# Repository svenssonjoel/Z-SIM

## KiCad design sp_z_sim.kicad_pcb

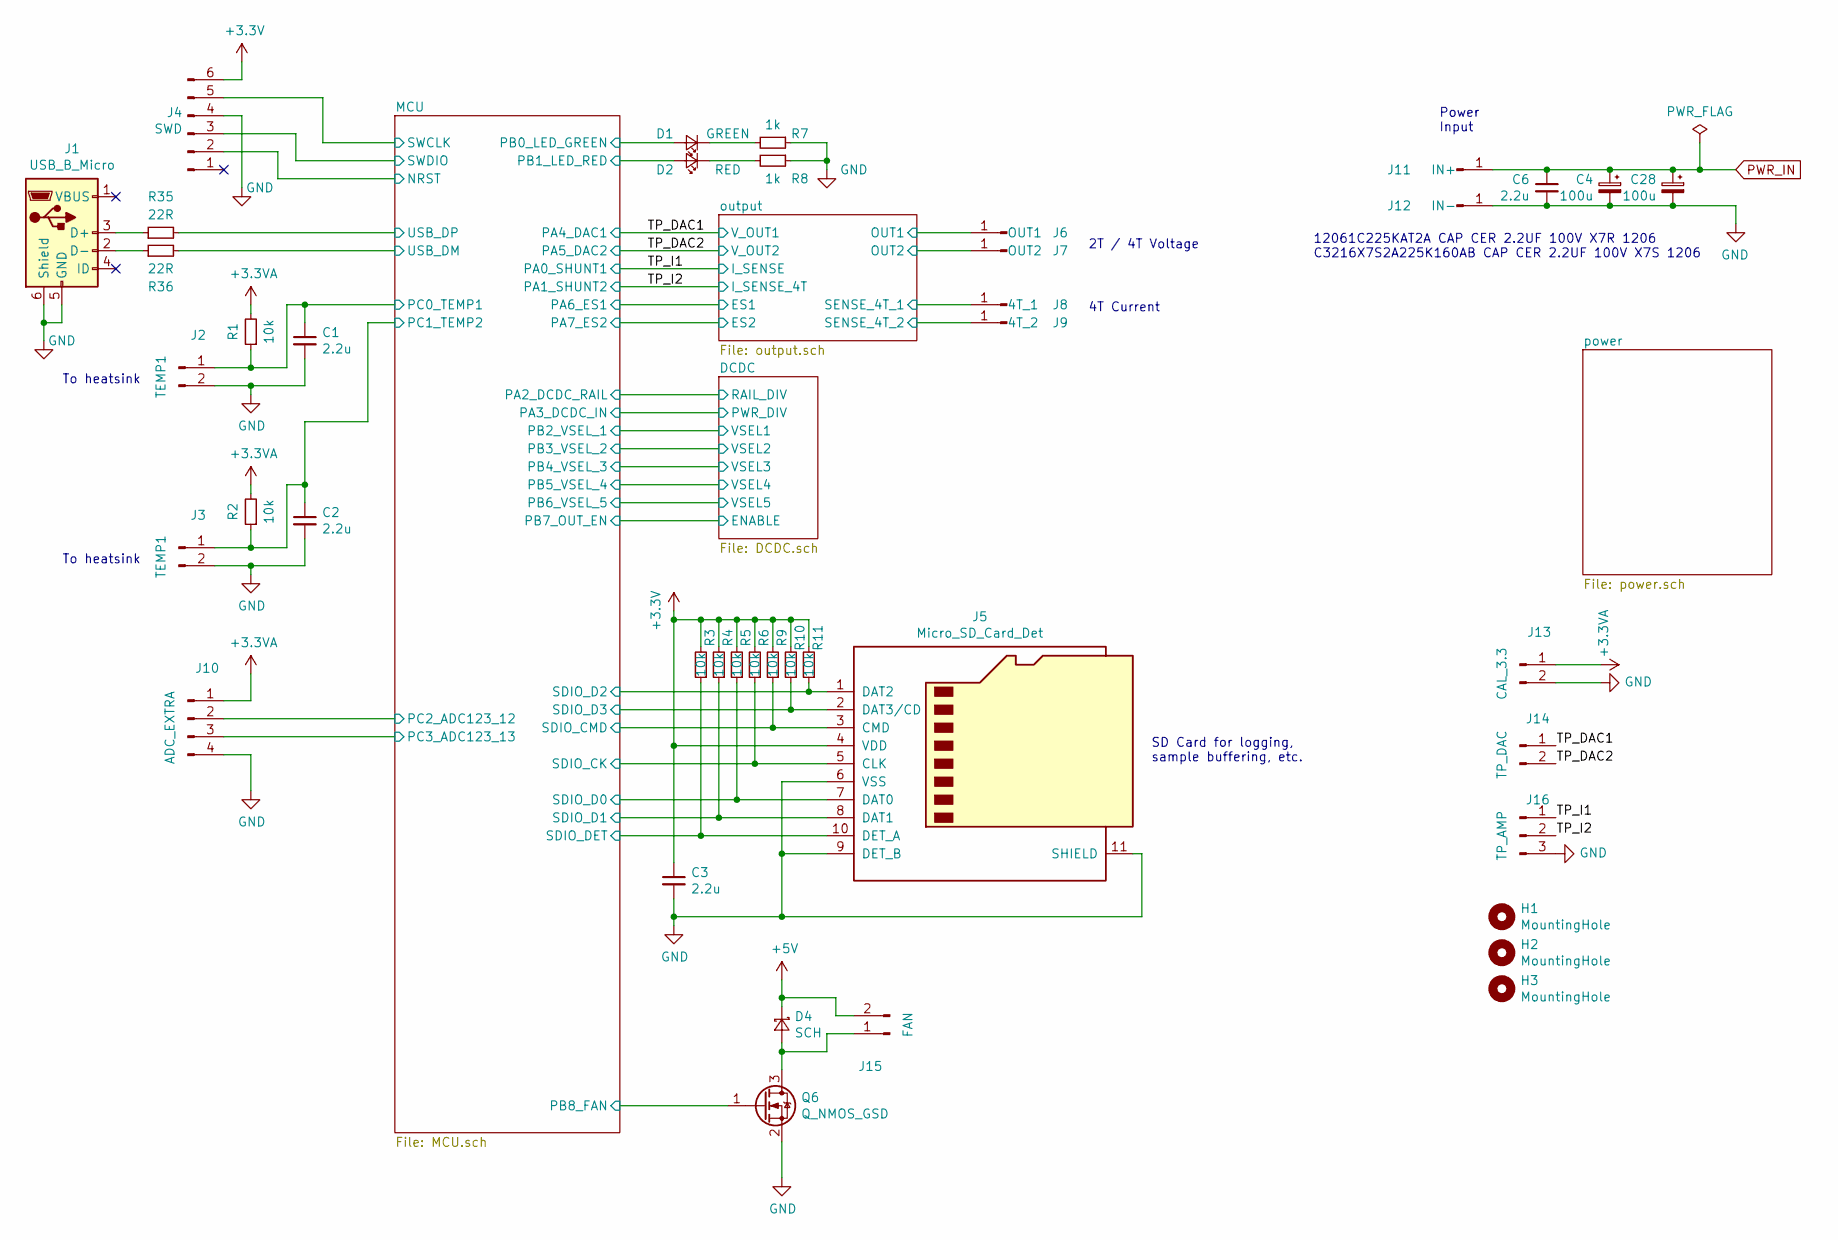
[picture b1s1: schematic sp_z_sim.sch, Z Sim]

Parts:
C1, C2, C3: 2.2u; C_0603_1608Metric
C4, C28: 100u; CP_Radial_D10.0mm_P5.00mm
C6: 2.2u; C_1206_3216Metric
D1: GREEN; LED_0603_1608Metric
D2: RED; LED_0603_1608Metric
D4: SCH; D_SMA
H1, H2, H3: MountingHole; MountingHole_3.2mm_M3
J1: USB_B_Micro; USB_Micro-B_Molex-105017-0001
J2, J3: TEMP1; JST_PH_B2B-PH-K_1x02_P2.00mm_Vertical
J4: SWD; JST_PH_B6B-PH-K_1x06_P2.00mm_Vertical
J5: Micro_SD_Card_Det; microSD_HC_Hirose_DM3D-SF
J6: OUT1; TestPoint_Pad_4.0x4.0mm
J7: OUT2; TestPoint_Pad_4.0x4.0mm
J8: 4T_1; TestPoint_Pad_4.0x4.0mm
J9: 4T_2; TestPoint_Pad_4.0x4.0mm
J10: ADC_EXTRA; JST_PH_B4B-PH-K_1x04_P2.00mm_Vertical
J11: IN+; TestPoint_Pad_4.0x4.0mm
J12: IN-; TestPoint_Pad_4.0x4.0mm
J13: CAL_3.3; JST_PH_B2B-PH-K_1x02_P2.00mm_Vertical
J14: TP_DAC; JST_PH_B2B-PH-K_1x02_P2.00mm_Vertical
J15: FAN; JST_PH_B2B-PH-K_1x02_P2.00mm_Vertical
J16: TP_AMP; JST_PH_B3B-PH-K_1x03_P2.00mm_Vertical
Q6: Q_NMOS_GSD; SOT-23
R1, R2, R3, R4, R5, R6, R9, R10, R11: 10k; R_0603_1608Metric
R7, R8: 1k; R_0603_1608Metric
R35, R36: 22R; R_0603_1608Metric

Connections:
+3.3VA: J10.1, J13.1, R1.2, R2.2; also elsewhere on the board
+3V3: C3.1, J4.6, J5.4 (VDD), R3.2, R4.2, R5.2, R6.2, R9.2, R10.2, R11.2; also elsewhere on the board
+5V: D4.1 (K), J15.2; also elsewhere on the board
/NRST: J4.2; also elsewhere on the board
/OUT1: J6.1; also elsewhere on the board
/OUT2: J7.1; also elsewhere on the board
/PB0_LED_GREEN: D1.2 (A); also elsewhere on the board
/PB1_LED_RED: D2.2 (A); also elsewhere on the board
/PB8_FAN: Q6.1 (G); also elsewhere on the board
/PC0_TEMP1: C1.1, J2.1, R1.1; also elsewhere on the board
/PC1_TEMP2: C2.1, J3.1, R2.1; also elsewhere on the board
/PC2_ADC123_12: J10.2; also elsewhere on the board
/PC3_ADC123_13: J10.3; also elsewhere on the board
/SDIO_CK: J5.5 (CLK), R6.1; also elsewhere on the board
/SDIO_CMD: J5.3 (CMD), R9.1; also elsewhere on the board
/SDIO_D0: J5.7 (DAT0), R5.1; also elsewhere on the board
/SDIO_D1: J5.8 (DAT1), R4.1; also elsewhere on the board
/SDIO_D2: J5.1 (DAT2), R11.1; also elsewhere on the board
/SDIO_D3: J5.2 (DAT3/CD), R10.1; also elsewhere on the board
/SDIO_DET: J5.10 (DET_A), R3.1; also elsewhere on the board
/SENSE_4T_1: J8.1; also elsewhere on the board
/SENSE_4T_2: J9.1; also elsewhere on the board
/SWCLK: J4.5; also elsewhere on the board
/SWDIO: J4.3; also elsewhere on the board
/TP_DAC1: J14.1; also elsewhere on the board
/TP_DAC2: J14.2; also elsewhere on the board
/TP_I1: J16.1; also elsewhere on the board
/TP_I2: J16.2; also elsewhere on the board
/USB_DM: R36.2; also elsewhere on the board
/USB_DP: R35.2; also elsewhere on the board
GND: C1.2, C2.2, C3.2, C4.2, C6.2, C28.2, J1.5 (GND), J1.6 (Shield), J2.2, J3.2, J4.4, J5.6 (VSS), J5.9 (DET_B), J5.11 (SHIELD), J10.4, J12.1, J13.2, J16.3, Q6.2 (S), R7.1, R8.1; also elsewhere on the board
unnamed: D1.1 (K), R7.2
unnamed: D2.1 (K), R8.2
unnamed: D4.2 (A), J15.1, Q6.3 (D)
unnamed: J1.2 (D-), R36.1
unnamed: J1.3 (D+), R35.1
PWR_IN: C4.1, C6.1, C28.1, J11.1; also elsewhere on the board

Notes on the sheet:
To heatsink
2T / 4T Voltage
4T Current
12061C225KAT2A CAP CER 2.2UF 100V X7R 1206 C3216X7S2A225K160AB CAP CER 2.2UF 100V X7S 1206
Power Input
SD Card for logging, sample buffering, etc.

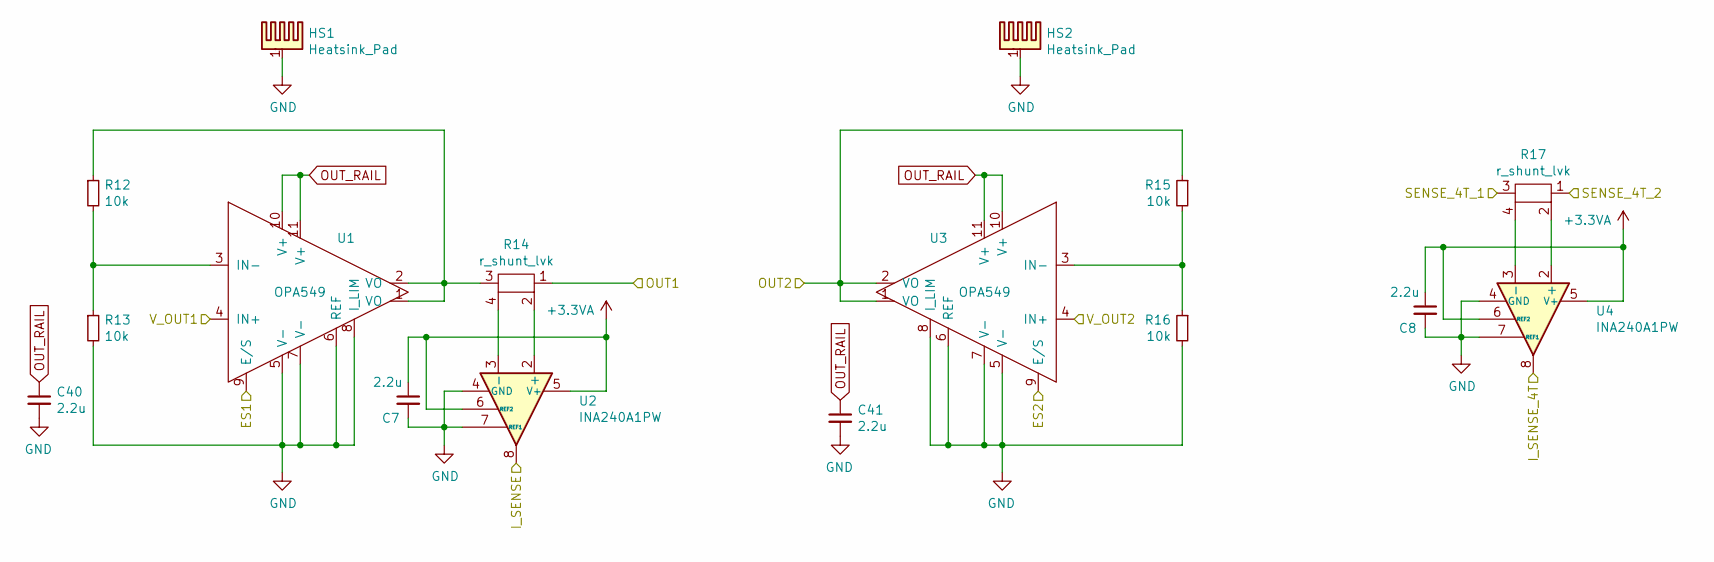
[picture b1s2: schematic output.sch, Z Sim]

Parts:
C7, C8, C40, C41: 2.2u; C_0603_1608Metric
HS1, HS2: Heatsink_Pad; OMNI-220-18-50-2C
R12, R13, R15, R16: 10k; R_0603_1608Metric
R14, R17: r_shunt_lvk; R_Shunt_Ohmite_LVK24
U1, U3: OPA549; TO-220-11_P3.4x5.08mm_StaggerOdd_Lead4.85mm_Vertical
U2, U4: INA240A1PW; TSSOP-8_4.4x3mm_P0.65mm

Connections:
+3.3VA: C7.1, C8.1, U2.5 (V+), U2.6 (REF2), U4.5 (V+), U4.6 (REF2); also elsewhere on the board
/OUT1: R14.1; also elsewhere on the board
/OUT2: R15.1, U3.1 (VO), U3.2 (VO); also elsewhere on the board
/PA6_ES1: U1.9 (E/S); also elsewhere on the board
/PA7_ES2: U3.9 (E/S); also elsewhere on the board
/SENSE_4T_1: R17.3; also elsewhere on the board
/SENSE_4T_2: R17.1; also elsewhere on the board
/TP_DAC1: U1.4 (IN+); also elsewhere on the board
/TP_DAC2: U3.4 (IN+); also elsewhere on the board
/TP_I1: U2.8; also elsewhere on the board
/TP_I2: U4.8; also elsewhere on the board
GND: C7.2, C8.2, C40.2, C41.2, HS1.1, HS2.1, R13.2, R16.2, U1.5 (V-), U1.6 (REF), U1.7 (V-), U1.8 (I_LIM), U2.1 (GND), U2.4 (GND), U2.7 (REF1), U3.5 (V-), U3.6 (REF), U3.7 (V-), U3.8 (I_LIM), U4.1 (GND), U4.4 (GND), U4.7 (REF1); also elsewhere on the board
unnamed: R12.1, R14.3, U1.1 (VO), U1.2 (VO)
unnamed: R12.2, R13.1, U1.3 (IN-)
unnamed: R14.2, U2.2 (+)
unnamed: R14.4, U2.3 (-)
unnamed: R15.2, R16.1, U3.3 (IN-)
unnamed: R17.2, U4.2 (+)
unnamed: R17.4, U4.3 (-)
OUT_RAIL: C40.1, C41.1, U1.10 (V+), U1.11 (V+), U3.10 (V+), U3.11 (V+); also elsewhere on the board

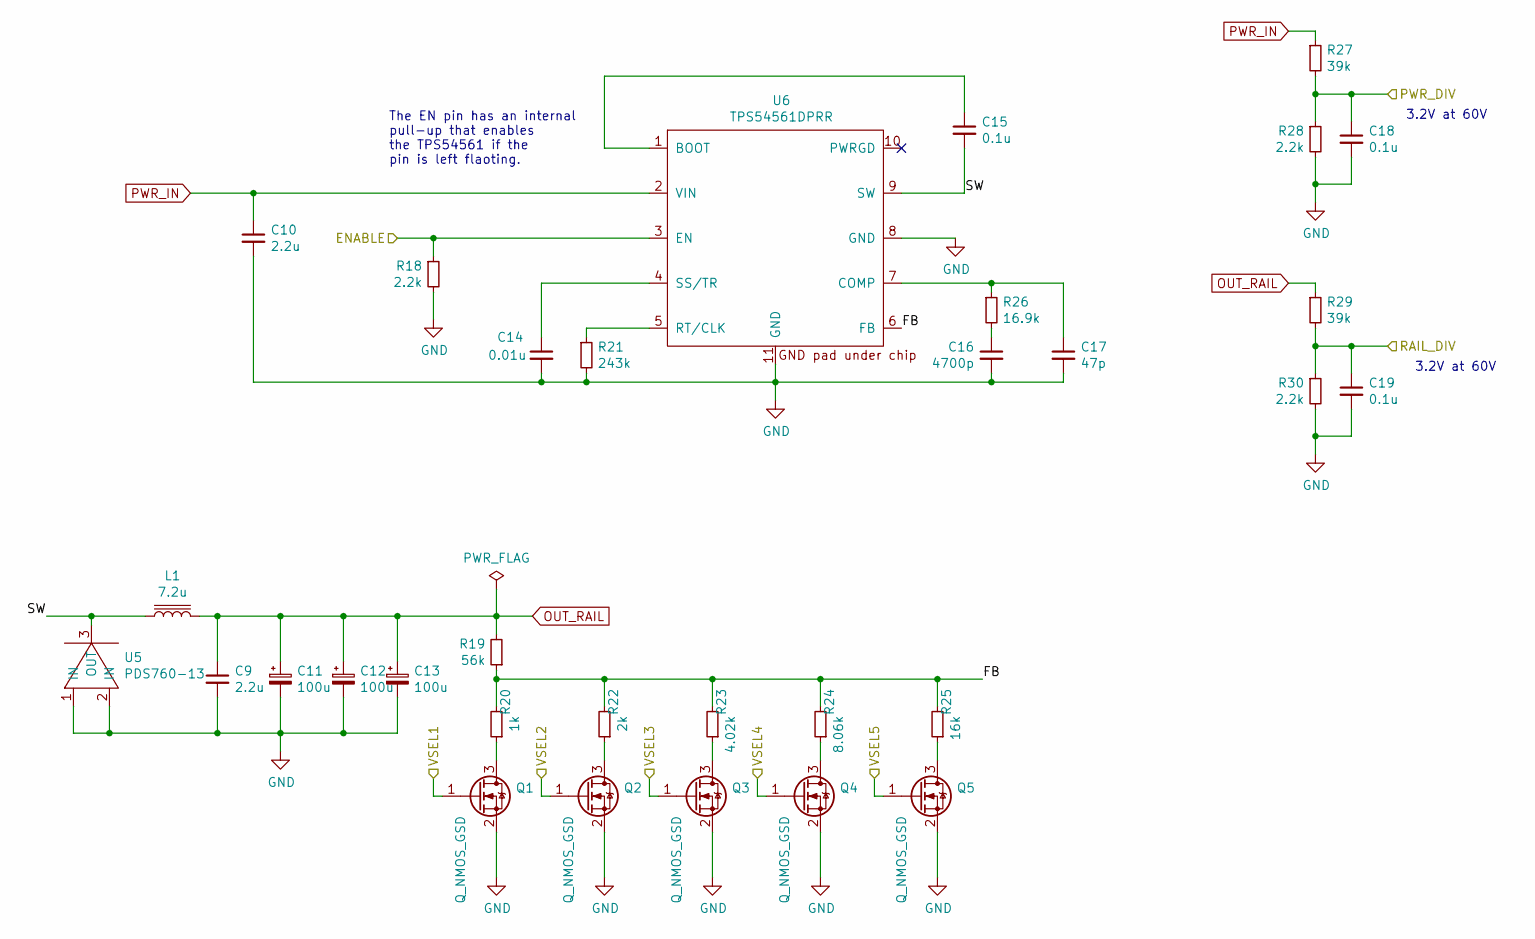
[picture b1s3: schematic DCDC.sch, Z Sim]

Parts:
C9: 2.2u; C_0603_1608Metric
C10: 2.2u; C_1206_3216Metric
C11, C12, C13: 100u; CP_Radial_D10.0mm_P5.00mm
C14: 0.01u; C_0603_1608Metric
C15, C18, C19: 0.1u; C_0603_1608Metric
C16: 4700p; C_0603_1608Metric
C17: 47p; C_0603_1608Metric
L1: 7.2u; L_12x12mm_H8mm
Q1, Q2, Q3, Q4, Q5: Q_NMOS_GSD; SOT-23
R18, R28, R30: 2.2k; R_0603_1608Metric
R19: 56k; R_0603_1608Metric
R20: 1k; R_0603_1608Metric
R21: 243k; R_0603_1608Metric
R22: 2k; R_0603_1608Metric
R23: 4.02k; R_0603_1608Metric
R24: 8.06k; R_0603_1608Metric
R25: 16k; R_0603_1608Metric
R26: 16.9k; R_0603_1608Metric
R27, R29: 39k; R_0603_1608Metric
U5: PDS760-13; POWERDI5
U6: TPS54561DPRR; TI-DPR

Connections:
/DCDC/FB: R19.1, R20.2, R22.2, R23.2, R24.2, R25.2, U6.6 (FB)
/DCDC/SW: C15.2, L1.1, U5.3 (OUT), U6.9 (SW)
/ENABLE: R18.1, U6.3 (EN); also elsewhere on the board
/PA2_DCDC_RAIL: C19.1, R29.2, R30.1; also elsewhere on the board
/PB2_VSEL_1: Q1.1 (G); also elsewhere on the board
/PB3_VSEL_2: Q2.1 (G); also elsewhere on the board
/PB4_VSEL_3: Q3.1 (G); also elsewhere on the board
/PWR_DIV: C18.1, R27.2, R28.1; also elsewhere on the board
/VSEL4: Q4.1 (G); also elsewhere on the board
/VSEL5: Q5.1 (G); also elsewhere on the board
GND: C9.2, C10.2, C11.2, C12.2, C13.2, C14.2, C16.2, C17.2, C18.2, C19.2, Q1.2 (S), Q2.2 (S), Q3.2 (S), Q4.2 (S), Q5.2 (S), R18.2, R21.2, R28.2, R30.2, U5.1 (IN), U5.2 (IN), U6.8 (GND), U6.11 (GND); also elsewhere on the board
unnamed: C14.1, U6.4 (SS/TR)
unnamed: C15.1, U6.1 (BOOT)
unnamed: C16.1, R26.2
unnamed: C17.1, R26.1, U6.7 (COMP)
unnamed: Q1.3 (D), R20.1
unnamed: Q2.3 (D), R22.1
unnamed: Q3.3 (D), R23.1
unnamed: Q4.3 (D), R24.1
unnamed: Q5.3 (D), R25.1
unnamed: R21.1, U6.5 (RT/CLK)
OUT_RAIL: C9.1, C11.1, C12.1, C13.1, L1.2, R19.2, R29.1; also elsewhere on the board
PWR_IN: C10.1, R27.1, U6.2 (VIN); also elsewhere on the board

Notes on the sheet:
3.2V at 60V
The EN pin has an internal pull-up that enables the TPS54561 if the pin is left flaoting.

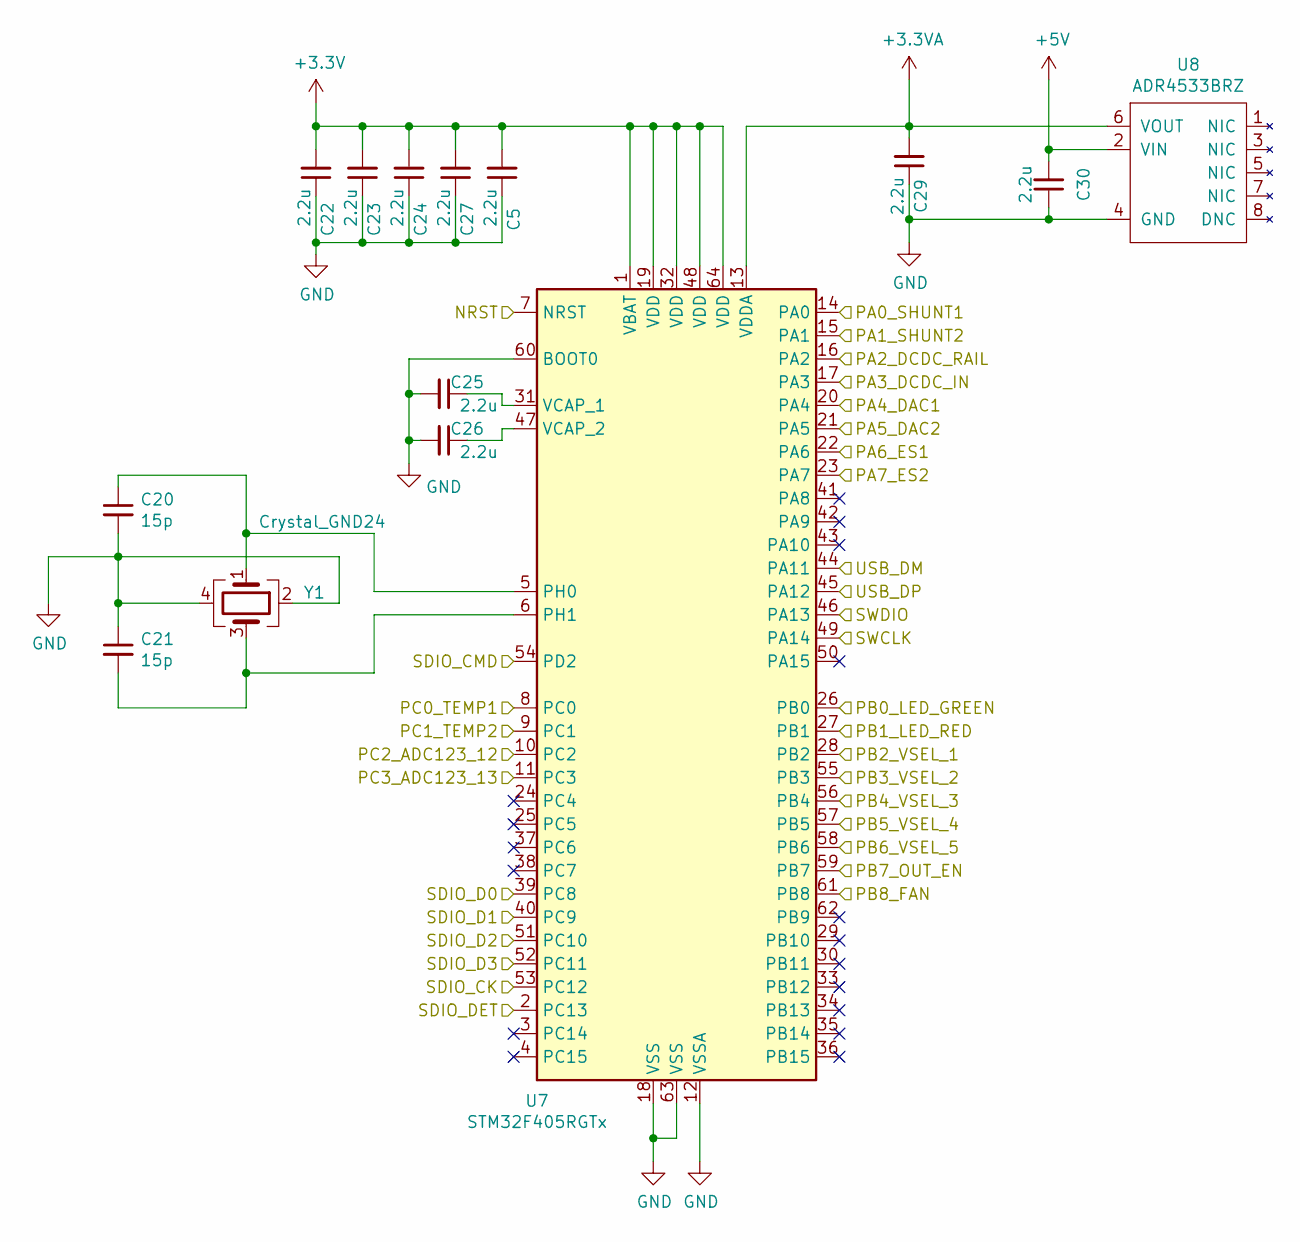
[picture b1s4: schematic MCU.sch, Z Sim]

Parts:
C5, C22, C23, C24, C25, C26, C27, C29, C30: 2.2u; C_0603_1608Metric
C20, C21: 15p; C_0603_1608Metric
U7: STM32F405RGTx; LQFP-64_10x10mm_P0.5mm
U8: ADR4533BRZ; SOIC-8_3.9x4.9mm_P1.27mm
Y1: Crystal_GND24; Crystal_SMD_Abracon_ABM3C-4Pin_5.0x3.2mm

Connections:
+3.3VA: C29.2, U7.13 (VDDA), U8.6 (VOUT); also elsewhere on the board
+3V3: C5.2, C22.2, C23.2, C24.2, C27.2, U7.1 (VBAT), U7.19 (VDD), U7.32 (VDD), U7.48 (VDD), U7.64 (VDD); also elsewhere on the board
+5V: C30.2, U8.2 (VIN); also elsewhere on the board
/ENABLE: U7.59 (PB7); also elsewhere on the board
/NRST: U7.7 (NRST); also elsewhere on the board
/PA2_DCDC_RAIL: U7.16 (PA2); also elsewhere on the board
/PA6_ES1: U7.22 (PA6); also elsewhere on the board
/PA7_ES2: U7.23 (PA7); also elsewhere on the board
/PB0_LED_GREEN: U7.26 (PB0); also elsewhere on the board
/PB1_LED_RED: U7.27 (PB1); also elsewhere on the board
/PB2_VSEL_1: U7.28 (PB2); also elsewhere on the board
/PB3_VSEL_2: U7.55 (PB3); also elsewhere on the board
/PB4_VSEL_3: U7.56 (PB4); also elsewhere on the board
/PB8_FAN: U7.61 (PB8); also elsewhere on the board
/PC0_TEMP1: U7.8 (PC0); also elsewhere on the board
/PC1_TEMP2: U7.9 (PC1); also elsewhere on the board
/PC2_ADC123_12: U7.10 (PC2); also elsewhere on the board
/PC3_ADC123_13: U7.11 (PC3); also elsewhere on the board
/PWR_DIV: U7.17 (PA3); also elsewhere on the board
/SDIO_CK: U7.53 (PC12); also elsewhere on the board
/SDIO_CMD: U7.54 (PD2); also elsewhere on the board
/SDIO_D0: U7.39 (PC8); also elsewhere on the board
/SDIO_D1: U7.40 (PC9); also elsewhere on the board
/SDIO_D2: U7.51 (PC10); also elsewhere on the board
/SDIO_D3: U7.52 (PC11); also elsewhere on the board
/SDIO_DET: U7.2 (PC13); also elsewhere on the board
/SWCLK: U7.49 (PA14); also elsewhere on the board
/SWDIO: U7.46 (PA13); also elsewhere on the board
/TP_DAC1: U7.20 (PA4); also elsewhere on the board
/TP_DAC2: U7.21 (PA5); also elsewhere on the board
/TP_I1: U7.14 (PA0); also elsewhere on the board
/TP_I2: U7.15 (PA1); also elsewhere on the board
/USB_DM: U7.44 (PA11); also elsewhere on the board
/USB_DP: U7.45 (PA12); also elsewhere on the board
/VSEL4: U7.57 (PB5); also elsewhere on the board
/VSEL5: U7.58 (PB6); also elsewhere on the board
GND: C5.1, C20.2, C21.1, C22.1, C23.1, C24.1, C25.2, C26.2, C27.1, C29.1, C30.1, U7.12 (VSSA), U7.18 (VSS), U7.60 (BOOT0), U7.63 (VSS), U8.4 (GND), Y1.2, Y1.4; also elsewhere on the board
unnamed: C20.1, U7.5 (PH0), Y1.1
unnamed: C21.2, U7.6 (PH1), Y1.3
unnamed: C25.1, U7.31 (VCAP_1)
unnamed: C26.1, U7.47 (VCAP_2)

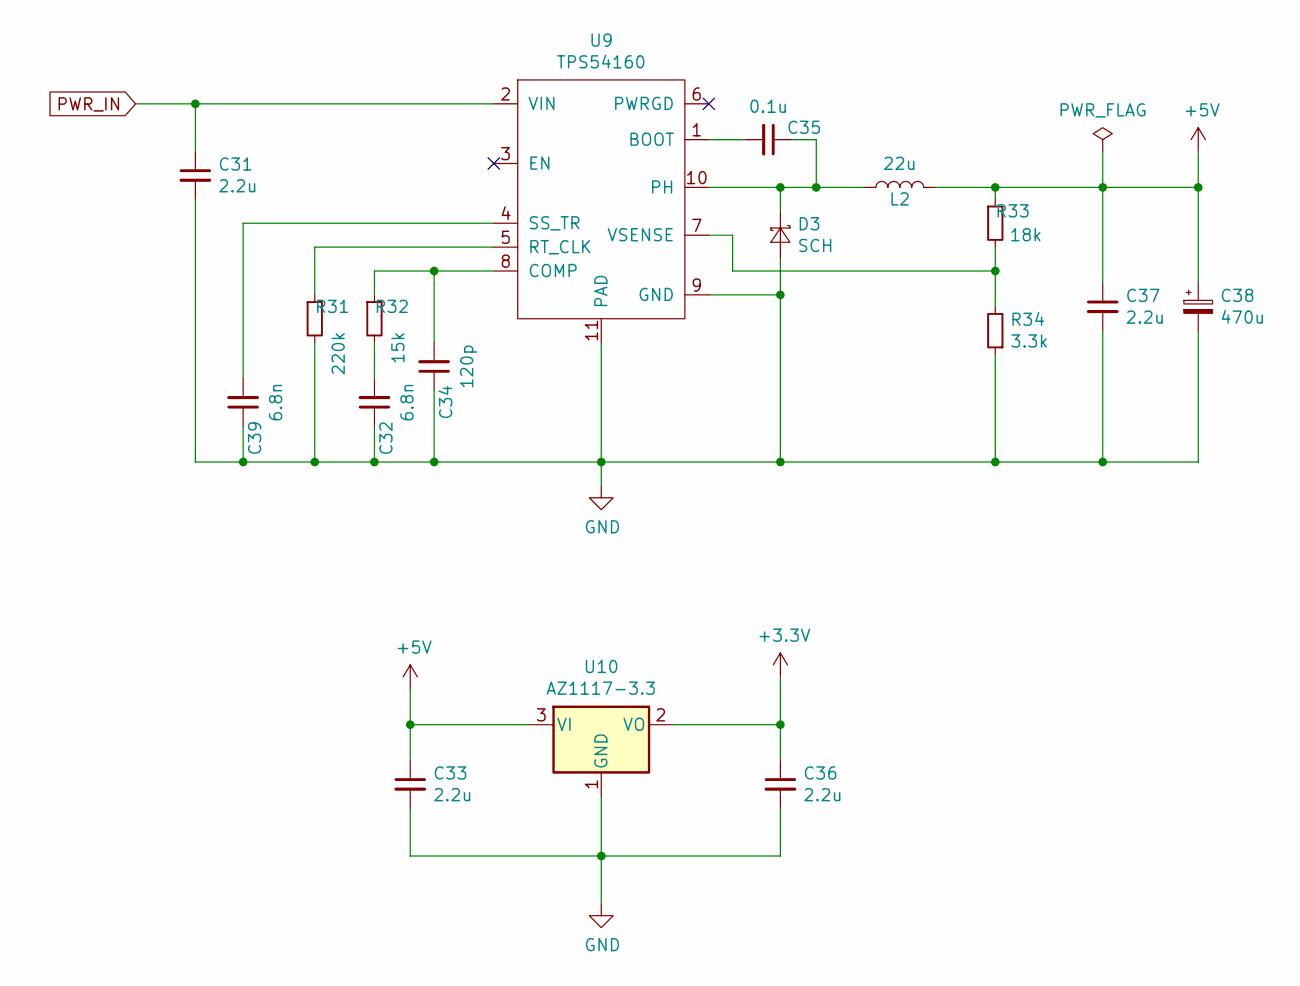
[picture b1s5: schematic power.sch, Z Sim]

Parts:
C31, C33, C36, C37: 2.2u; C_1206_3216Metric
C32, C39: 6.8n; C_0603_1608Metric
C34: 120p; C_0603_1608Metric
C35: 0.1u; C_0603_1608Metric
C38: 470u; CP_Radial_D10.0mm_P5.00mm
D3: SCH; D_SMA
L2: 22u; L_Taiyo-Yuden_NR-60xx_HandSoldering
R31: 220k; R_0603_1608Metric
R32: 15k; R_0603_1608Metric
R33: 18k; R_0603_1608Metric
R34: 3.3k; R_0603_1608Metric
U9: TPS54160; MSOP-10-1EP_3x3mm_P0.5mm_EP1.68x1.88mm
U10: AZ1117-3.3; SOT-223

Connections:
+3V3: C36.1, U10.2 (VO); also elsewhere on the board
+5V: C33.1, C37.1, C38.1, L2.2, R33.1, U10.3 (VI); also elsewhere on the board
GND: C31.2, C32.1, C33.2, C34.1, C36.2, C37.2, C38.2, C39.1, D3.2 (A), R31.2, R34.1, U9.9 (GND), U9.11 (PAD), U10.1 (GND); also elsewhere on the board
unnamed: C32.2, R32.2
unnamed: C34.2, R32.1, U9.8 (COMP)
unnamed: C35.1, D3.1 (K), L2.1, U9.10 (PH)
unnamed: C35.2, U9.1 (BOOT)
unnamed: C39.2, U9.4 (SS_TR)
unnamed: R31.1, U9.5 (RT_CLK)
unnamed: R33.2, R34.2, U9.7 (VSENSE)
PWR_IN: C31.1, U9.2 (VIN); also elsewhere on the board

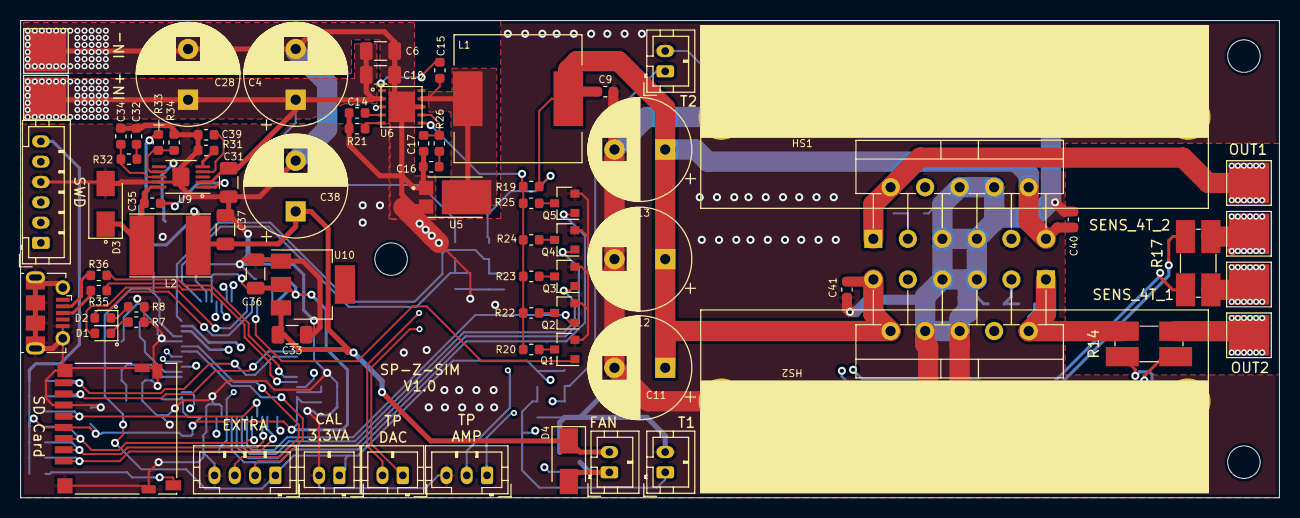
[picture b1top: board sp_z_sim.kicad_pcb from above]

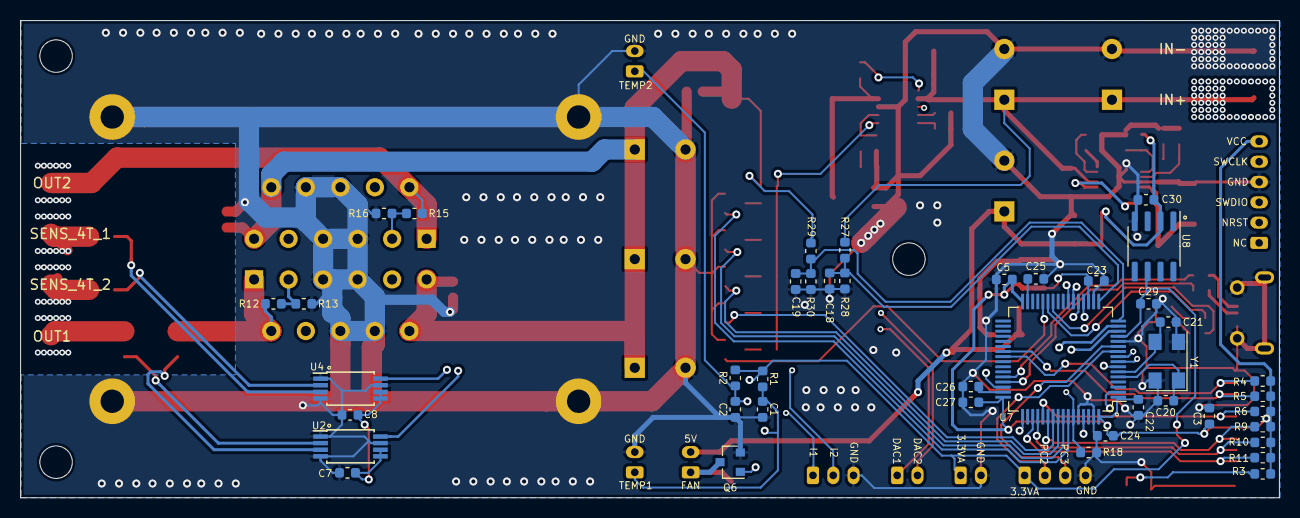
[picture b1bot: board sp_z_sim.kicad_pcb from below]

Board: 4 copper layers, 124.0 x 47.0 mm, 121 parts (42 on the bottom side), 78 nets.

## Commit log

2019-10-21 initial commit: work in progress
2019-10-22 Finished first version of schematic
2019-10-23 preparation for routing and adding kylfläns
2019-10-24 Schematic updates, added 3D models and started routing
2019-10-24 Some routing updates
2019-11-04 Finished routing and added some 3D models
2019-11-05 Updated heatsink footprint
2019-11-05 Updated solder mask settings
2019-11-05 Added PCB name to silkscreen
2019-11-05 almost done with bom. there are some issues
2019-11-07 Added testpoints, changed connectors, changed shunts
2019-11-08 Finished routing and added gerber files
2019-11-18 added new resistances for the resistance ladder-thingy
2019-11-18 all components now have an OrderN in the matrix
2019-11-18 Changed fan mosfet part number
2019-11-22 tweak component matrix
2019-12-05 moved around text on fab layer
2019-12-15 starting with setyup of a firmware directory and adding some essentials. No Z-Sim is complete without a Lisp interpreter.
2019-12-15 adding more essentials
2019-12-15 added flash rule to makefile
2019-12-15 small tweak to openocd config file
2019-12-15 started construction of a driver for the dcdc block
2019-12-15 added dcdc-enable/disable capabilities from Lisp interpreter
2019-12-17 changed FMRC to Z-SIM
